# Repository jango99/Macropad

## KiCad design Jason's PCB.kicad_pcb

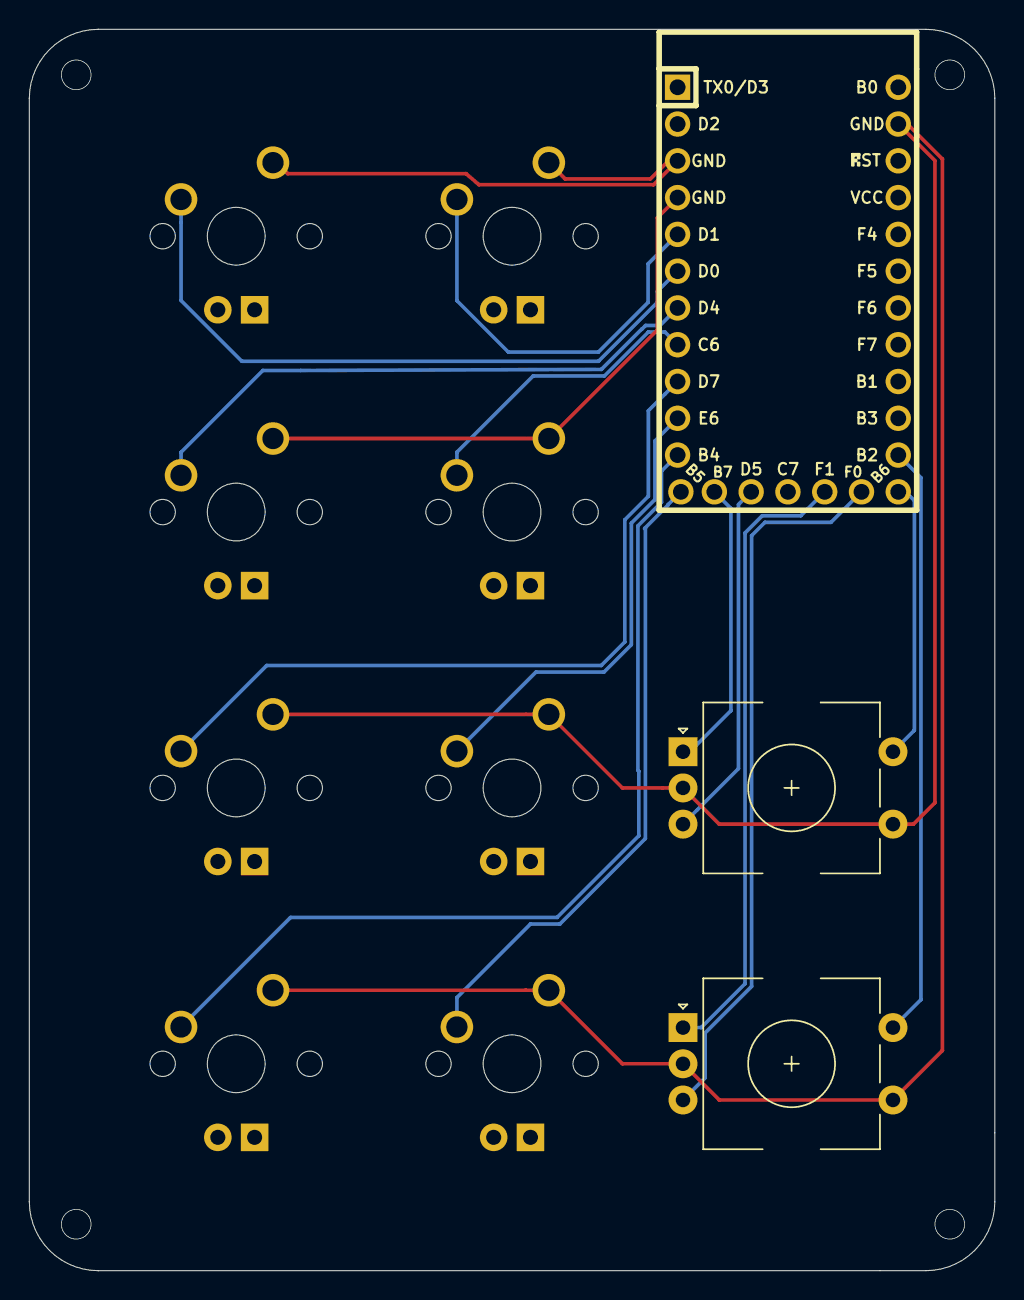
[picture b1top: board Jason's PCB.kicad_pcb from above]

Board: 2 copper layers, 66.7 x 85.7 mm, 11 parts (0 on the bottom side), 15 nets.

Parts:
SW_A1, SW_A2: MX_LED; MXOnly-1U
SW_B1, SW_B2: MX_LED; MXOnly-1U
SW_C1, SW_C2: MX_LED; MXOnly-1U
SW_D1, SW_D2: MX_LED; MXOnly-1U
SW_E1, SW_E2: Rotary_Encoder_Switch; RotaryEncoder_EC11
U1: Elite-C

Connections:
Enc1A: SW_E1.A, U1.25
Enc1B: SW_E1.B, U1.26
Enc2A: SW_E2.A, U1.28
Enc2B: SW_E2.B, U1.29
GND: SW_A1.2, SW_A2.2, SW_B1.2, SW_B2.2, SW_C1.2, SW_C2.2, SW_D1.2, SW_D2.2, SW_E1.C, SW_E1.S1, SW_E2.C, SW_E2.S1, U1.3, U1.4, U1.23
SWA1: SW_A1.1, U1.6
SWA2: SW_A2.1, U1.5
SWB1: SW_B1.1, U1.7
SWB2: SW_B2.1, U1.8
SWC1: SW_C1.1, U1.9
SWC2: SW_C2.1, U1.10
SWC3: SW_E1.S2, U1.13
SWD1: SW_D1.1, U1.11
SWD2: SW_D2.1, U1.12
SWD3: SW_E2.S2, U1.14

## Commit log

2019-12-18 Kicad PCB schematics
2019-12-18 Add submodules
2019-12-18 More submodules
2019-12-18 Added footprint/symbol libraries
2019-12-18 Schematic Diagram
2019-12-18 Schematic updates
2019-12-19 Schematic/PCB General Shape
    -Added 2 rotary encoder
    -Simplified PCB. No need for diodes.
    -Added outside edges of PCB
2019-12-19 Formatting
    -Changes some labels
2019-12-19 Revert "Formatting"
    This reverts commit f1c91c2560923d7a35fc048f965f097b1ceabb0f.
2019-12-21 Adjusted rotary encoder placements
2019-12-21 Edge cut changes
    - Consistent 4.76 mm bezel around switches
2019-12-25 Routing
    -Changed nets in schematic to make routing easier
2019-12-28 More routing changes
2019-12-31 Initial SVG sandwich mount commit
2020-01-01 Created .stl of .svg files for case
2020-01-17 gerber updates
2020-01-18 Fixed Drills/gerbers
2020-02-10 QMK_firmware added
2020-02-16 Renamed project/remade case
2020-03-02 fixed encoder
2020-03-02 changed binds
